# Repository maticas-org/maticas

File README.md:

# Maticas

Repositorio de huerta hidropónica automatizada. 
En esta rama trabajamos la sección de ***Software Web*** del proyecto, la estructura de las carpetas es:

* ***styling***, carpeta que guarda todas las constantes de estilo.

* ***widgets***, contiene los widgets que se van creando.

* ***images***, guarda imagenes y otros recursos que se usan en la pagina web.

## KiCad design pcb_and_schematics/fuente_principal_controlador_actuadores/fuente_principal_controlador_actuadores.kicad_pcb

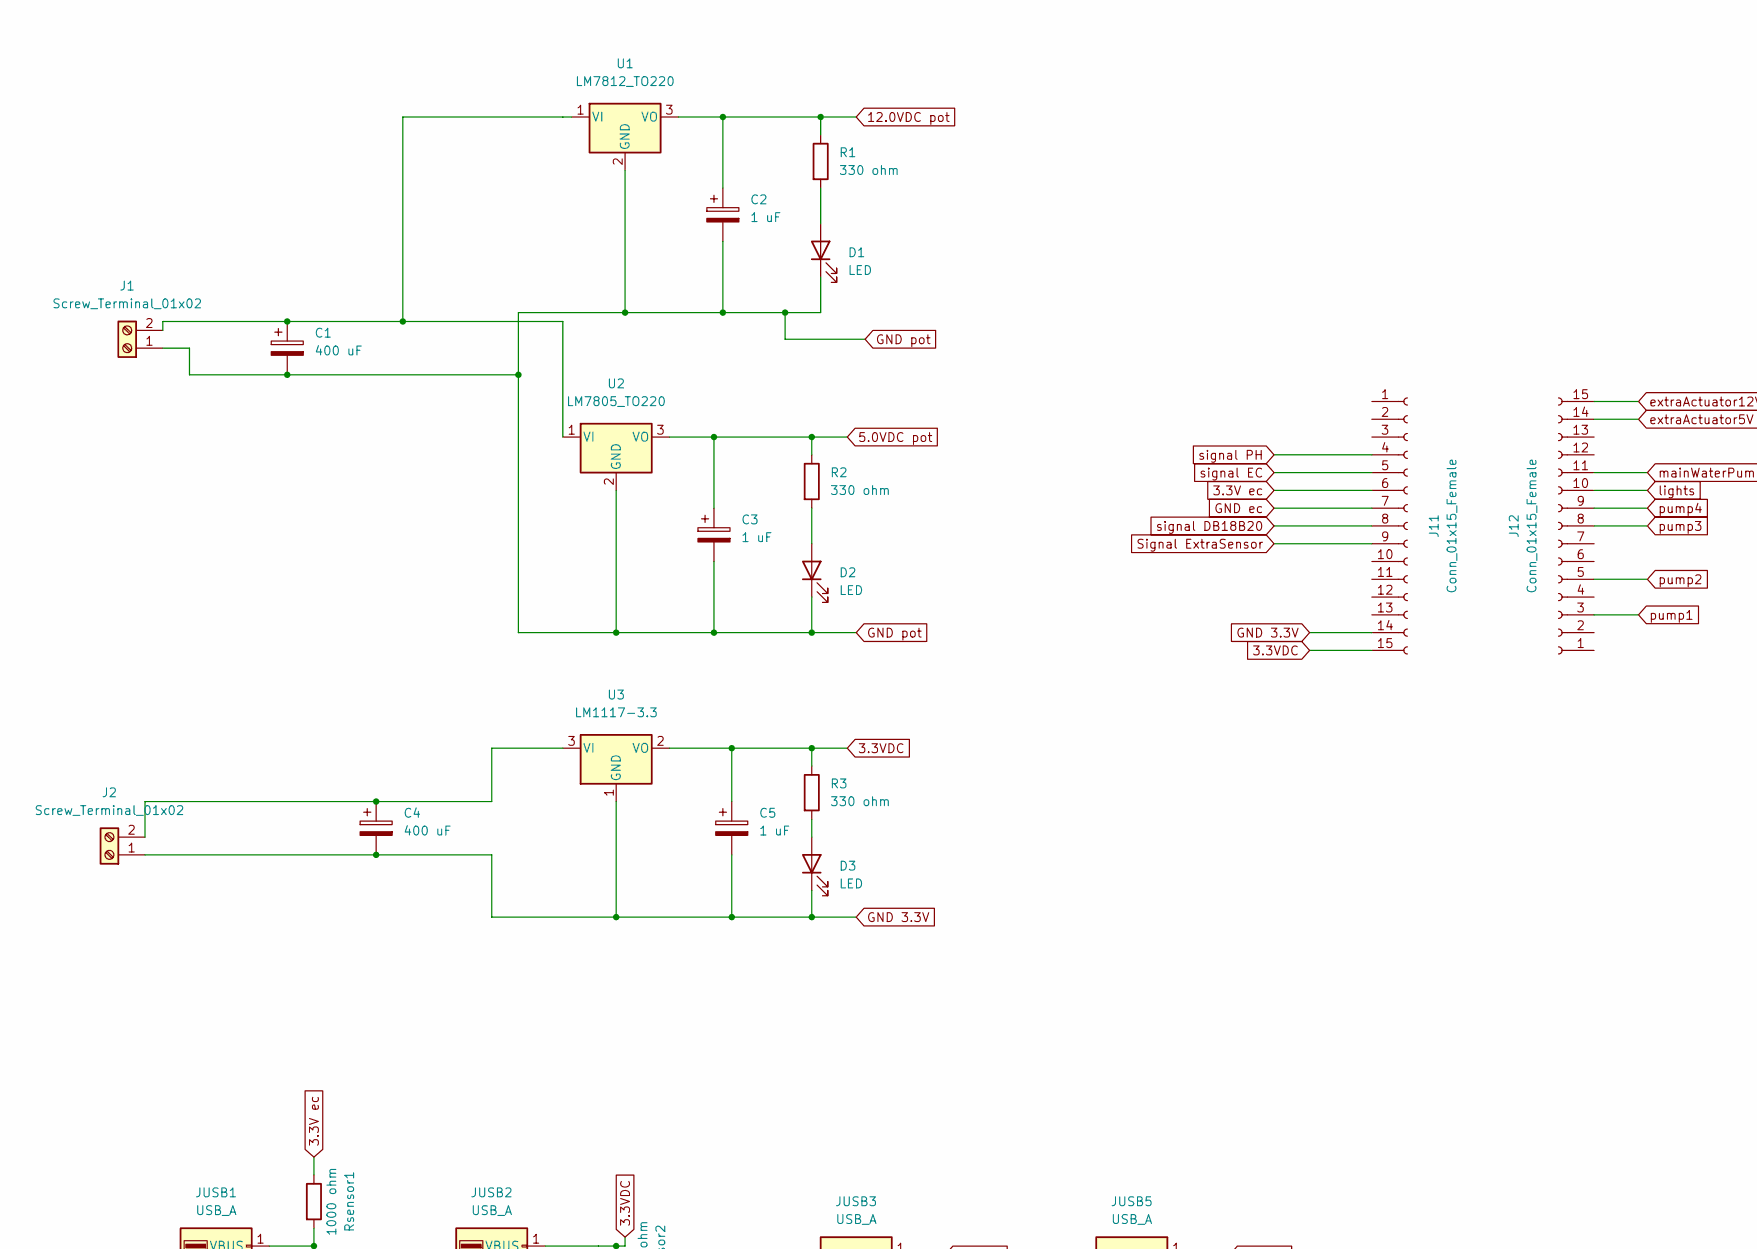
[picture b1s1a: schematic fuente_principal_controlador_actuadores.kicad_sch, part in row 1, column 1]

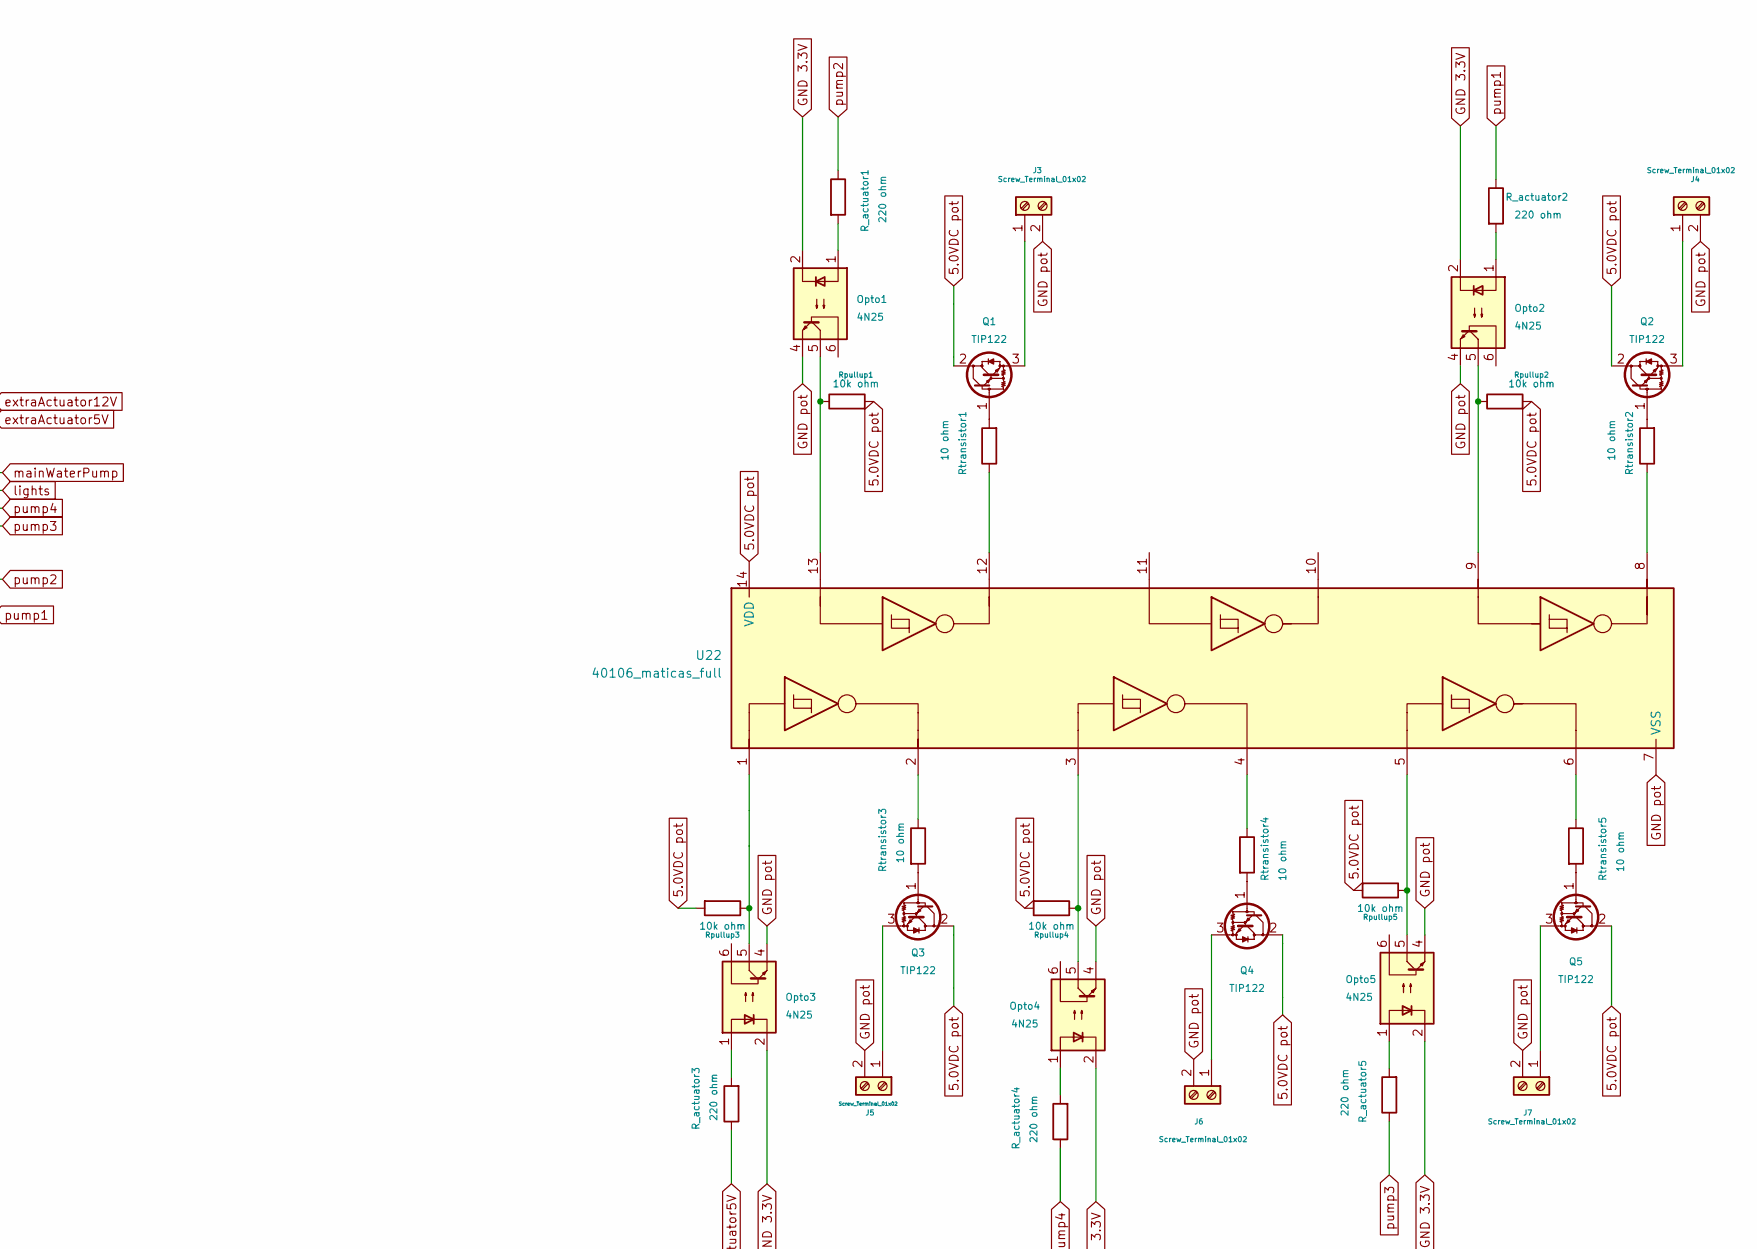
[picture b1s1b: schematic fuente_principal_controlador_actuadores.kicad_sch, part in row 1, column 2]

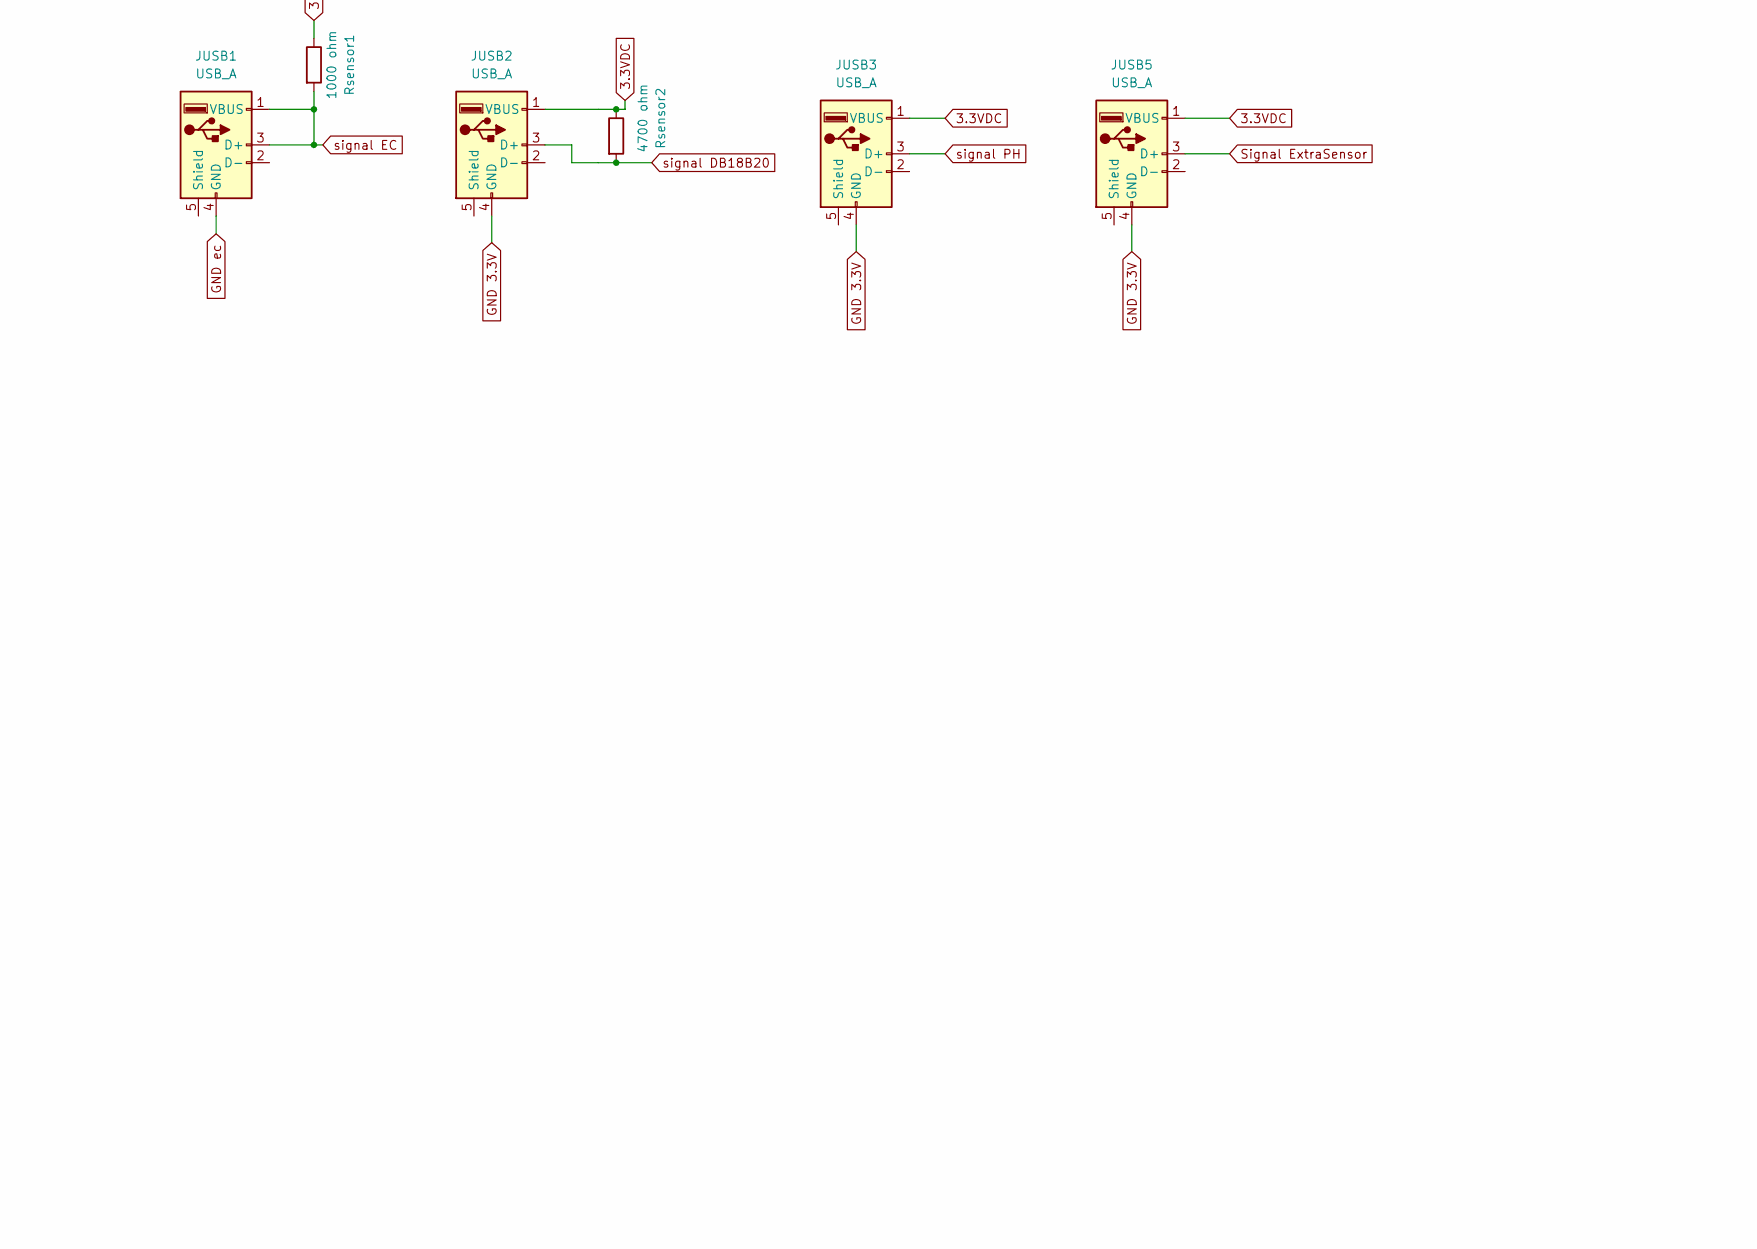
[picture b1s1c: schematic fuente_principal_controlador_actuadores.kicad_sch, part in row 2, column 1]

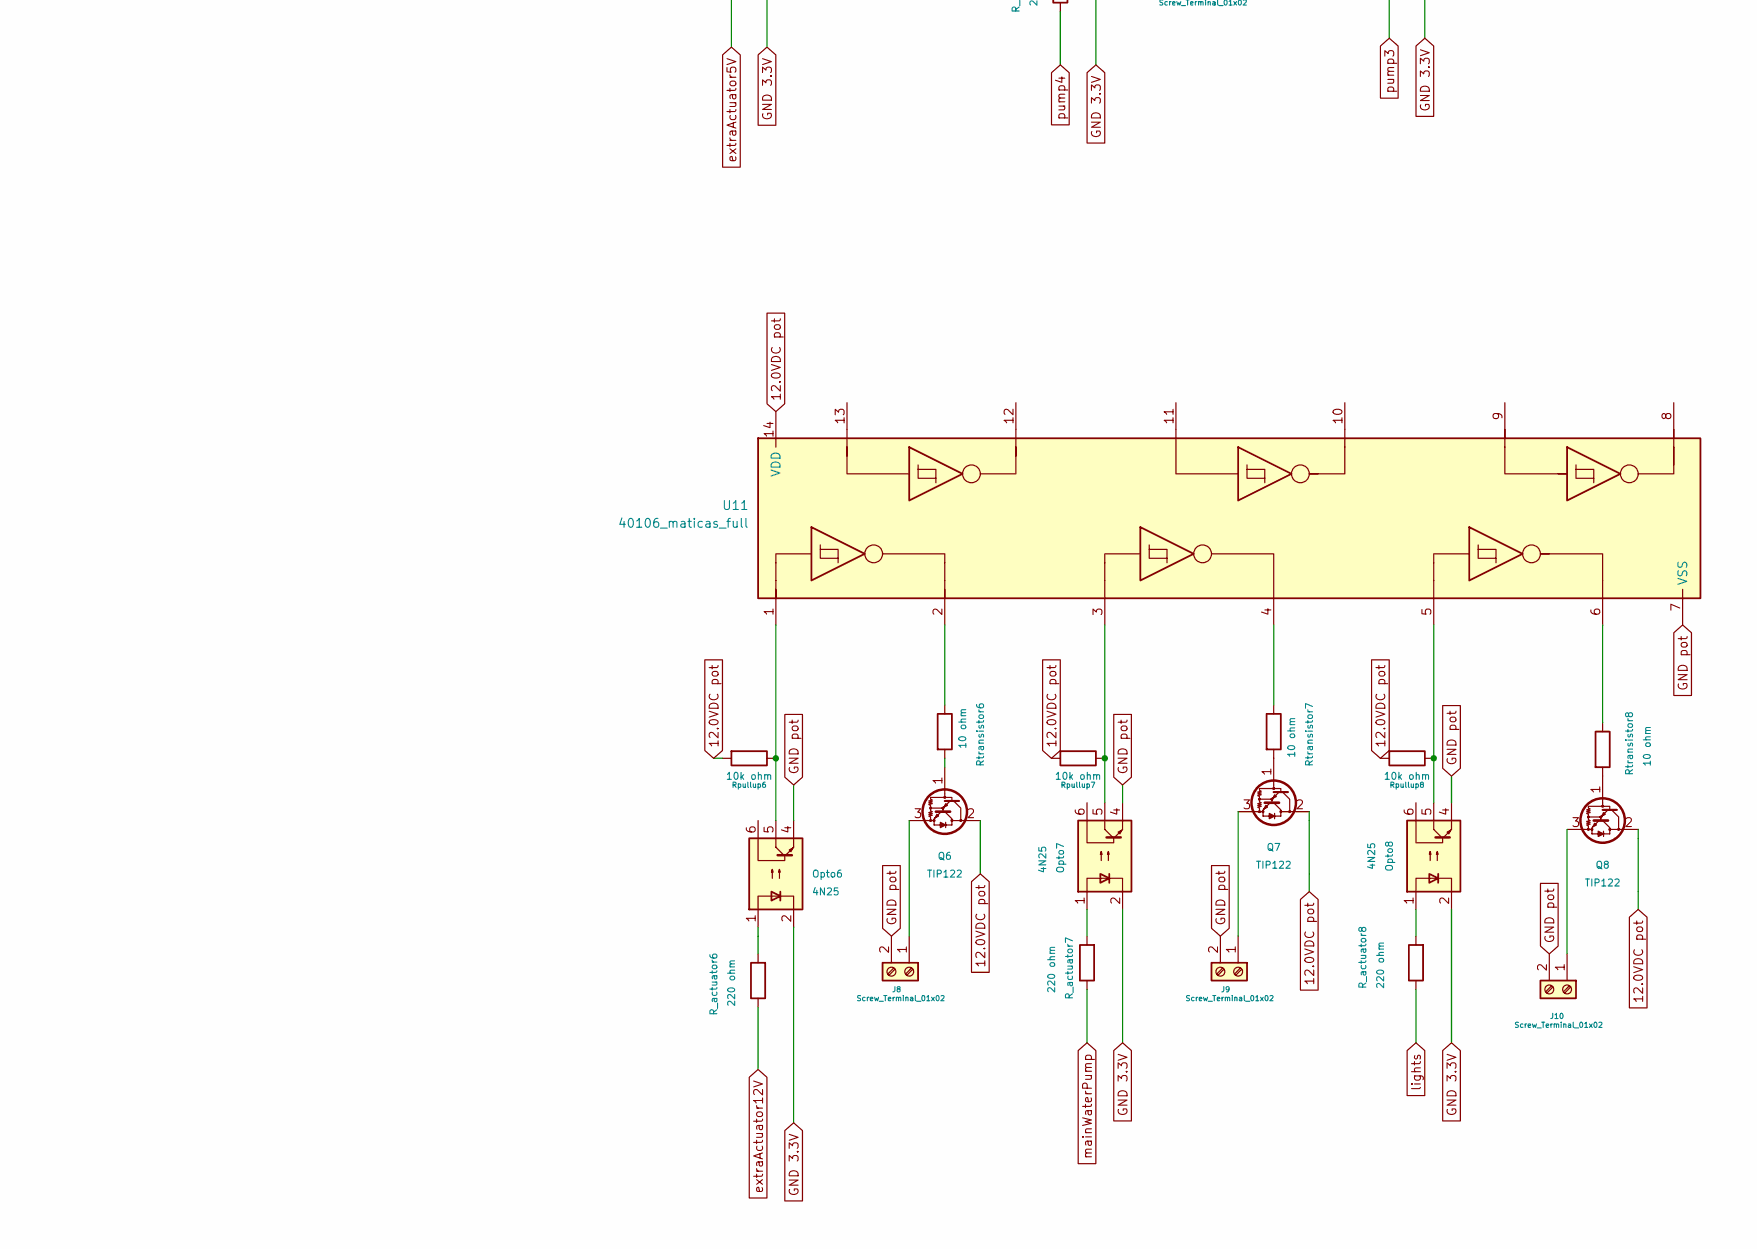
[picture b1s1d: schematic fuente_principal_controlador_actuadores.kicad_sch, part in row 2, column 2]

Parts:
C1, C4: 400 uF; electrolitic_capacitor_470uF
C2, C3, C5: 1 uF; electrolitic_capacitor_470uF
D1, D2, D3: LED; LED_D3.0mm
J1, J2, J3, J4, J5, J6, J7, J8, J9, J10: Screw_Terminal_01x02; actuators_screws_01x02_low_pot
J11, J12: Conn_01x15_Female; PinSocket_1x15_P1.27mm_Vertical
JUSB1, JUSB2, JUSB3, JUSB5: USB_A; USB_A_Molex_67643_Horizontal
Opto1, Opto2, Opto3, Opto4, Opto5, Opto6, Opto7, Opto8: 4N25; DIP-6_W7.62mm
Q1, Q2, Q3, Q4, Q5, Q6, Q7, Q8: TIP122; tip122_more_clearence
R1, R2, R3: 330 ohm; R_Axial_DIN0204_L3.6mm_D1.6mm_P5.08mm_Horizontal
R_actuator1, R_actuator2, R_actuator3, R_actuator4, R_actuator5, R_actuator6, R_actuator7, R_actuator8: 220 ohm; R_Axial_DIN0204_L3.6mm_D1.6mm_P5.08mm_Horizontal
Rpullup1, Rpullup2, Rpullup3, Rpullup4, Rpullup5, Rpullup6, Rpullup7, Rpullup8: 10k ohm; R_Axial_DIN0207_L6.3mm_D2.5mm_P7.62mm_Horizontal
Rsensor1: 1000 ohm; R_Axial_DIN0204_L3.6mm_D1.6mm_P5.08mm_Horizontal
Rsensor2: 4700 ohm; R_Axial_DIN0204_L3.6mm_D1.6mm_P5.08mm_Horizontal
Rtransistor1, Rtransistor2, Rtransistor3, Rtransistor4, Rtransistor5, Rtransistor6, Rtransistor7, Rtransistor8: 10 ohm; R_Axial_DIN0207_L6.3mm_D2.5mm_P7.62mm_Horizontal
U1: LM7812_TO220; tip122_more_clearence
U2: LM7805_TO220; tip122_more_clearence
U3: LM1117-3.3; tip122_more_clearence
U11, U22: 40106_maticas_full

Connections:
3.3V ec: J11.6, Rsensor1.1
3.3VDC: C5.1, J11.15, JUSB2.1 (VBUS), JUSB3.1 (VBUS), JUSB5.1 (VBUS), R3.1, Rsensor2.1, U3.2 (VO)
5.0VDC pot: C3.1, Q1.2 (C), Q2.2 (C), Q3.2 (C), Q4.2 (C), Q5.2 (C), R2.1, Rpullup1.2, Rpullup2.2, Rpullup3.2, Rpullup4.2, Rpullup5.2, U2.3 (VO), U22.14 (VDD)
12.0VDC pot: C2.1, Q6.2 (C), Q7.2 (C), Q8.2 (C), R1.1, Rpullup6.2, Rpullup7.2, Rpullup8.2, U1.3 (VO), U11.14 (VDD)
GND 3.3V: C4.2, C5.2, D3.1 (K), J2.1, J11.14, JUSB2.4 (GND), JUSB3.4 (GND), JUSB5.4 (GND), Opto1.2, Opto2.2, Opto3.2, Opto4.2, Opto5.2, Opto6.2, Opto7.2, Opto8.2, U3.1 (GND)
GND ec: J11.7, JUSB1.4 (GND)
GND pot: C1.2, C2.2, C3.2, D1.1 (K), D2.1 (K), J1.1, J3.2, J4.2, J5.2, J6.2, J7.2, J8.2, J9.2, J10.2, Opto1.4, Opto2.4, Opto3.4, Opto4.4, Opto5.4, Opto6.4, Opto7.4, Opto8.4, U1.2 (GND), U2.2 (GND), U11.7 (VSS), U22.7 (VSS)
unnamed: C1.1, J1.2, U1.1 (VI), U2.1 (VI)
unnamed: C4.1, J2.2, U3.3 (VI)
unnamed: D1.2 (A), R1.2
unnamed: D2.2 (A), R2.2
unnamed: D3.2 (A), R3.2
unnamed: J3.1, Q1.3 (E)
unnamed: J4.1, Q2.3 (E)
unnamed: J5.1, Q3.3 (E)
unnamed: J6.1, Q4.3 (E)
unnamed: J7.1, Q5.3 (E)
unnamed: J8.1, Q6.3 (E)
unnamed: J9.1, Q7.3 (E)
unnamed: J10.1, Q8.3 (E)
unnamed: Opto1.1, R_actuator1.2
unnamed: Opto1.5, Rpullup1.1, U22.13
unnamed: Opto2.1, R_actuator2.2
unnamed: Opto2.5, Rpullup2.1, U22.9
unnamed: Opto3.1, R_actuator3.2
unnamed: Opto3.5, Rpullup3.1, U22.1
unnamed: Opto4.1, R_actuator4.2
unnamed: Opto4.5, Rpullup4.1, U22.3
unnamed: Opto5.1, R_actuator5.2
unnamed: Opto5.5, Rpullup5.1, U22.5
unnamed: Opto6.1, R_actuator6.2
unnamed: Opto6.5, Rpullup6.1, U11.1
unnamed: Opto7.1, R_actuator7.2
unnamed: Opto7.5, Rpullup7.1, U11.3
unnamed: Opto8.1, R_actuator8.2
unnamed: Opto8.5, Rpullup8.1, U11.5
unnamed: Q1.1 (B), Rtransistor1.2
unnamed: Q2.1 (B), Rtransistor2.2
unnamed: Q3.1 (B), Rtransistor3.2
unnamed: Q4.1 (B), Rtransistor4.2
unnamed: Q5.1 (B), Rtransistor5.2
unnamed: Q6.1 (B), Rtransistor6.2
unnamed: Q7.1 (B), Rtransistor7.2
unnamed: Q8.1 (B), Rtransistor8.2
unnamed: Rtransistor1.1, U22.12
unnamed: Rtransistor2.1, U22.8
unnamed: Rtransistor3.1, U22.2
unnamed: Rtransistor4.1, U22.4
unnamed: Rtransistor5.1, U22.6
unnamed: Rtransistor6.1, U11.2
unnamed: Rtransistor7.1, U11.4
unnamed: Rtransistor8.1, U11.6
Signal ExtraSensor: J11.9, JUSB5.3 (D+)
extraActuator5V: J12.14, R_actuator3.1
extraActuator12V: J12.15, R_actuator6.1
lights: J12.10, R_actuator8.1
mainWaterPump: J12.11, R_actuator7.1
pump1: J12.3, R_actuator2.1
pump2: J12.5, R_actuator1.1
pump3: J12.8, R_actuator5.1
pump4: J12.9, R_actuator4.1
signal DB18B20: J11.8, JUSB2.3 (D+), Rsensor2.2
signal EC: J11.5, JUSB1.1 (VBUS), JUSB1.3 (D+), Rsensor1.2
signal PH: J11.4, JUSB3.3 (D+)

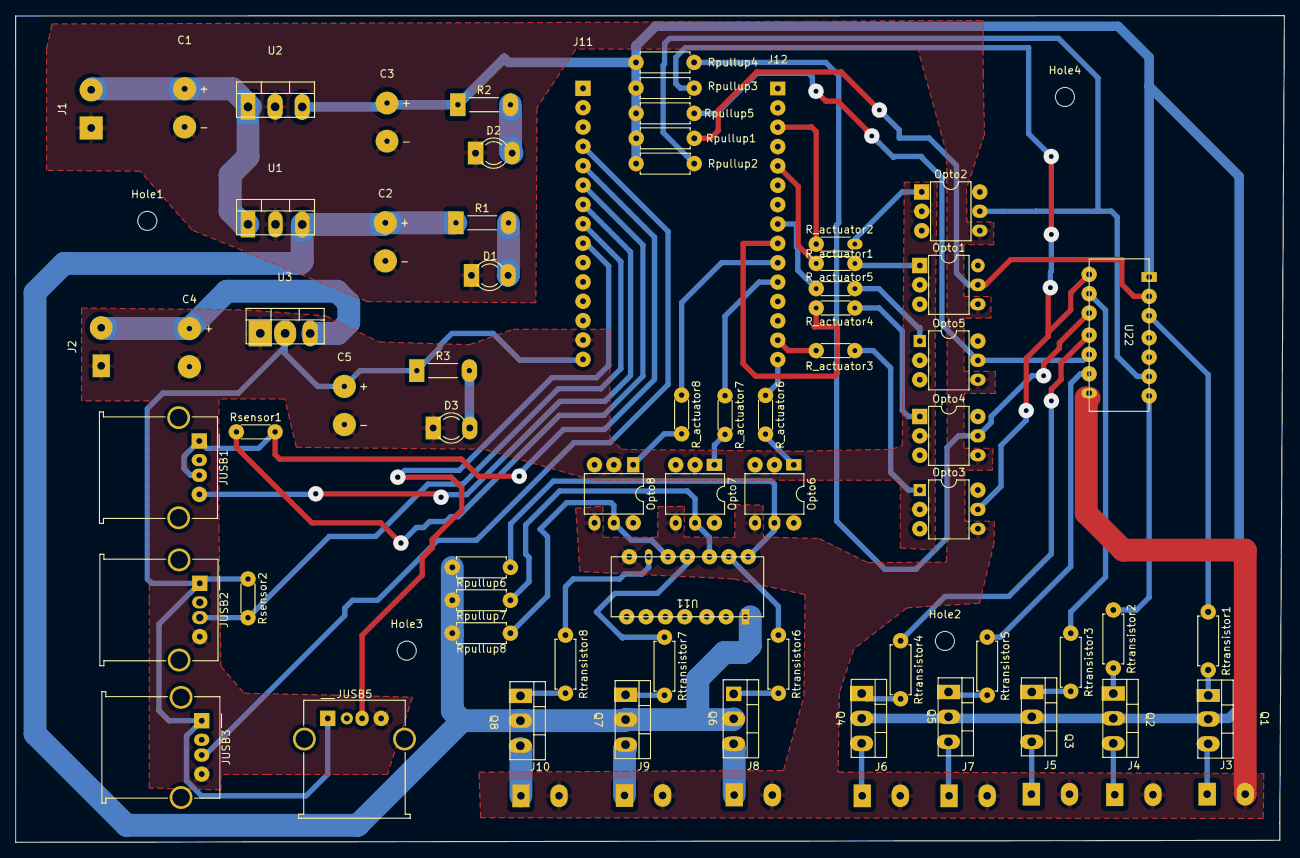
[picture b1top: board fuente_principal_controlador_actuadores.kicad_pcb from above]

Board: 2 copper layers, 166.5 x 108.5 mm, 78 parts (0 on the bottom side), 64 nets.

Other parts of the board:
Hole1, Hole2, Hole3, Hole4: MountingHole_2.5mm

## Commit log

2022-02-22 readme inicial
2022-02-22 readme de la rama
2022-02-22 readme parcialmente modificado
2022-02-23 creacion de subcarpetas
2022-02-23 creacion de archivos iniciales
2022-03-09 archivos nuevos para la conexión al broker hive
2022-03-09 sensor bme280 y bh1750
2022-04-02 conexión completada entre la base de datos y el broker mqtt con credenciales
2022-04-02 importantisimo gitignore
2022-04-02 pequeñas correcciones a la función de queries
2022-04-13 controlador de las luces - encender y apagarlas
2022-04-13 renombramiento y creación de una clase para controlar la bomba de agua y la luz
2022-04-13 un poco más de comentarios
2022-04-13 comentario de la clase
2022-04-13 soporta control de las bombas peristalticas
2022-04-14 controlador de la bomba de agua, controlador de las bombas peristalticas
2022-04-15 bombas peristalticas controlables
2022-04-15 carpeta data con certificados
2022-04-15 comentado de funciones y creacion de un archivo aparte para crear las tablas necesarias
2022-04-15 reorganización de archivos para más fácil lectura y compresión
2022-04-15 corrección de pequeño error
2022-04-15 comentarios y funcionalidad de escribir a tablas de condiciones optimas y aceptables, así como leer su información
2022-04-15 tabla para guardar configuraciones de bombas de agua y luces
2022-04-15 funcionalidad añadida para guardar configuracion de bombas de agua y luces
2022-04-17 creación de tabla faltante
2022-04-17 función para inicializar tablas por defecto
2022-04-17 valores por defecto actualizados
2022-04-21 readme actualizado
2022-04-21 mejor comentado
2022-04-27 controlador de las luces combinado con controlador de la bomba de agua
2022-04-27 nuevos archivos ya actualizados
2022-05-03 renombramiento
2022-05-03 inicios del daemon que controla el cultivo remotamente
2022-05-04 script de daemon al 80%
2022-05-04 pequeño cambio en el tiempo de espera al acabar una orden emitida
2022-05-04 agrega adaptación a la zona de tiempo de boogtá
2022-05-08 no me acuerdo que hice en este archivo
2022-05-08 daemon mejorado
2022-05-11 Borrado de archivos innecesarios
2022-05-11 Se añadio la carpeta de la app
2022-05-11 Modificacion del main y del html para activar funcionalidad de los botones accionadores
2022-05-11 pequeño cambio al main en las rutas de los botones
2022-05-12 Se comentaron las funciones en los archivos y se modificaron las funciones que controlan el encender y el apagar de la bomba de agua y de las luces
2022-05-17 se agregó la parte de la pagina de detailed_analysis a la aplicacion
2022-05-18 version final de la pagina web
2022-05-18 cambios en dash
2022-05-22 intercambio de la logica de los botones de encendido y apagado
2022-05-22 cambio de como enviar mensajes mqtt al broker, cambio de nombre de la tabla de temperatura
2022-05-22 cambio de nombre de la tabla temperature
2022-05-22 mejoras al código del daemon, ahora se usa schedule para controlar timing de eventos y el codigo está más ordenado
2022-06-11 actualizaciones al daemon.py
2022-06-11 script para correr automaticamete el daemon y la interface db_mqtt, con un contrab
2022-06-11 reordenado de archivos
2022-06-11 renombramiento premerge para hacer la release
2022-06-11 renombramiento premerge del readme para hacer la release
2022-06-12 documentación más detallada - prerelease
2022-06-12 imagen de las conexiones del módulo
2022-06-15 schematics for new iteration
2022-06-15 revisión del circuito de pcb
2022-06-15 otros adelantos en el diseño de la pcb
2022-06-16 archivos - prerelease
2022-06-16 mosquitto configs
2022-06-16 docs
2022-06-16 docs fix
2022-06-16 rm script
2022-06-16 sutoscript
2022-06-16 autoscript
2022-06-16 move ssl create
2022-06-16 minimal change to pcb layout
2022-06-16 deletion of files added by error to the branch
2022-06-16 updates on pcb design
2022-06-16 update on documentation
2022-06-16 images for docs
2022-06-20 documentation pre-release
2022-06-20 modificando información de contacto
2022-06-21 agregado de botón para comprar un café
2022-06-21 addition of .json files to replace, the credential files used as .py before
2022-06-22 reestructuracion para archivos json
2022-06-23 code review and partial addition of logs for debugging purposes
2022-06-23 update al git ignore
2022-06-23 eliminado de fuente de alimentación en el circuito, debido a que se va a comprar una ya hecha
2022-06-24 mejoras en el circuito de control
2022-06-24 avances en diseño de la pcb, de control y medicion de ph, ec y temperatura del agua
2022-06-25 mosquitto local conf
2022-06-26 adelantos en la creacion de la pcb a partir de los esquematicos
2022-06-26 addition of compressed files of the collected data, namely: ec, ph, temp, wtemp, hum, pressure and lux
2022-06-26 new footprints added to the schematics, and save process before reestructuration of trigger schmith footprint and schematic
2022-06-27 everything looks kinda ready for pcb fixies
2022-06-27 pcb layout organized and ready for autorouting
2022-06-27 pre autorouting check backup
2022-06-28 resizing of pads that involve high currents
2022-06-28 addition of net classes, and changes in footprint of resistors
2022-06-28 test file
2022-06-29 reestructuration of the entire pcb for decreasing the occupied space
2022-06-29 reestructuration of the entire pcb for decreasing the occupied space2
2022-07-07 start moving code to micropython
2022-07-07 class for mqtt connection
2022-07-07 working mqtt connection and publish
2022-07-08 addition of new function to drop all ambiental data tables, and to insert default data into ambiental data tables
2022-07-08 reestructure .gitignore and addition of venv folder to .gitignore
2022-07-09 integration of ds18 and mqtt class
2022-07-09 update .git ingore
2022-07-09 code for ph sensor and integration to mqtt done
2022-07-09 updated configs
2022-07-10 reestructuration of pin connections in the schematic
2022-07-11 Credential centralization and docker working
2022-07-11 requirements updates
2022-07-11 ignore update (env)
2022-07-11 handling of actuators added to the code library
2022-07-11 integration of sensors and actuators, code reestructuration and modification
2022-07-12 fix and passcript (sync with 1.3.2 image)
2022-07-12 reestructuration of pin connections in the schematic, addition of shared ground lines, and recrease in anchor by 1 cm
2022-07-12 tiny error fix on the clearence of ground tracks
2022-07-13 updated size of vias true holes, to make them bigger
2022-07-13 corrections in order to adapt to manufacturer constraints, and correction of size and spacing on esp32 pins
2022-07-13 little resize of important esp pins pad
2022-07-14 little fixies, only remains to check for the horizontal spacing of the esp32 of 30 pins used here
2022-07-14 fix of pad size of some resistors and other elements
2022-07-16 70% of process of moving to SQLAlchemy done, some reestructuration is also done
2022-07-16 deletion of accidentally updloaded csvs, to save space
2022-07-16 deletion of now unnecesary files
2022-07-16 Transition to SQLAlchemy done, and now you can run the scripts inside /db from wherever you want, because of absolute path additions
2022-07-17 small code corrections
2022-07-17 update to mqttclient class, which does both operations of pub and sub in mosquitto, this is now a module by it's self
2022-07-17 reestructuration of the interface between database and the mosquitto client, now it's much simpler
2022-07-17 deletion of now unnecesary files, in order to make easy the reestructuration
2022-07-21 update readme files
2022-09-04 initial api commit
2022-09-04 deletion of innecesary files
2022-09-06 users table partially done
2022-09-06 started to add a way to generate an API KEY for the user
2022-09-11 fixed bugs in code
2022-09-11 outdated requirements
2022-09-11 deletion of deprecated modules
2022-09-11 updated version of micropython code
2022-09-11 solved error on requesting measurement
2022-09-11 deletion of unnecesary files
2022-09-12 update to work correclty
2023-04-01 Backend Init
2023-04-01 DB model creation.
2023-04-01 API init
    It already has some user creation related endpoints.
